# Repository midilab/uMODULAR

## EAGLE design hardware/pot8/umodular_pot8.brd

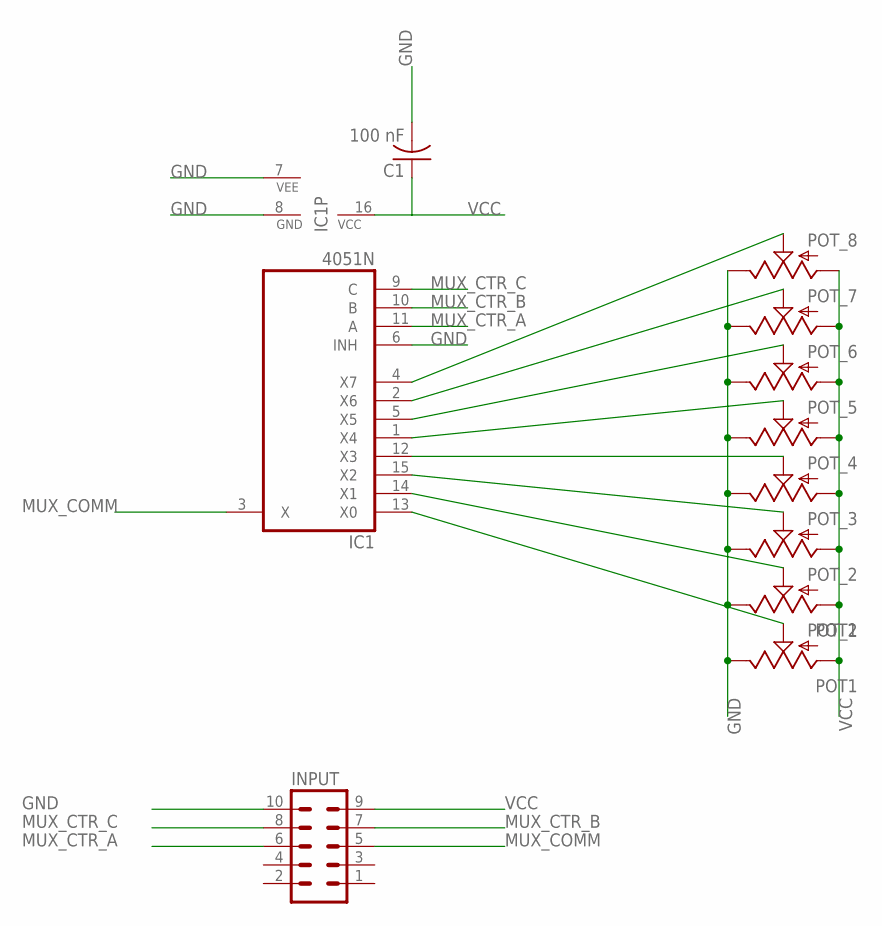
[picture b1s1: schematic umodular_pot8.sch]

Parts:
C1: 100 nF; C050-024X044
IC1: 4051N; DIL16
INPUT: MA05-2
POT_1: POT1; ALPS_POT
POT_2: POT2; ALPS_POT
POT_3, POT_4, POT_5, POT_6, POT_7, POT_8: POT; ALPS_POT

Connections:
GND: C1.2, IC1.6 (INH), IC1.7 (VEE), IC1.8 (GND), INPUT.10, POT_1.P$1 (E), POT_2.P$1 (E), POT_3.P$1 (E), POT_4.P$1 (E), POT_5.P$1 (E), POT_6.P$1 (E), POT_7.P$1 (E), POT_8.P$1 (E)
MUX_COMM: IC1.3 (X), INPUT.5
MUX_CTR_A: IC1.11 (A), INPUT.6
MUX_CTR_B: IC1.10 (B), INPUT.7
MUX_CTR_C: IC1.9 (C), INPUT.8
unnamed: IC1.5 (X5), POT_6.P$2 (S)
unnamed: IC1.2 (X6), POT_7.P$2 (S)
unnamed: IC1.13 (X0), POT_1.P$2 (S)
unnamed: IC1.14 (X1), POT_2.P$2 (S)
unnamed: IC1.15 (X2), POT_3.P$2 (S)
unnamed: IC1.12 (X3), POT_4.P$2 (S)
unnamed: IC1.1 (X4), POT_5.P$2 (S)
unnamed: IC1.4 (X7), POT_8.P$2 (S)
VCC: C1.1, IC1.16 (VCC), INPUT.9, POT_1.P$3 (A), POT_2.P$3 (A), POT_3.P$3 (A), POT_4.P$3 (A), POT_5.P$3 (A), POT_6.P$3 (A), POT_7.P$3 (A), POT_8.P$3 (A)

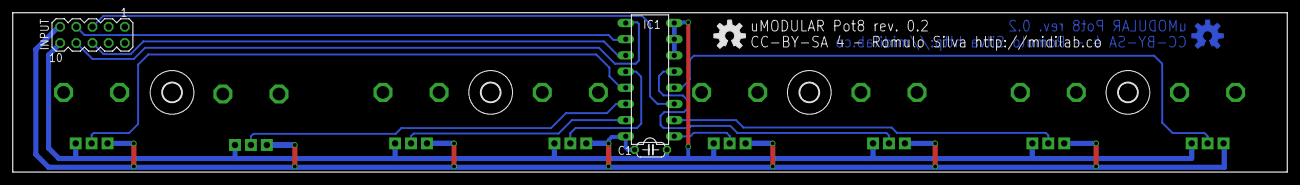
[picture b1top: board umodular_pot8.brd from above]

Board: 2 copper layers, 200.0 x 25.0 mm, 17 parts (0 on the bottom side), 14 nets.

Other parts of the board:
U$1, U$2, U$3, U$4: 3,0
U$5, U$6: OSHW-LOGO-M

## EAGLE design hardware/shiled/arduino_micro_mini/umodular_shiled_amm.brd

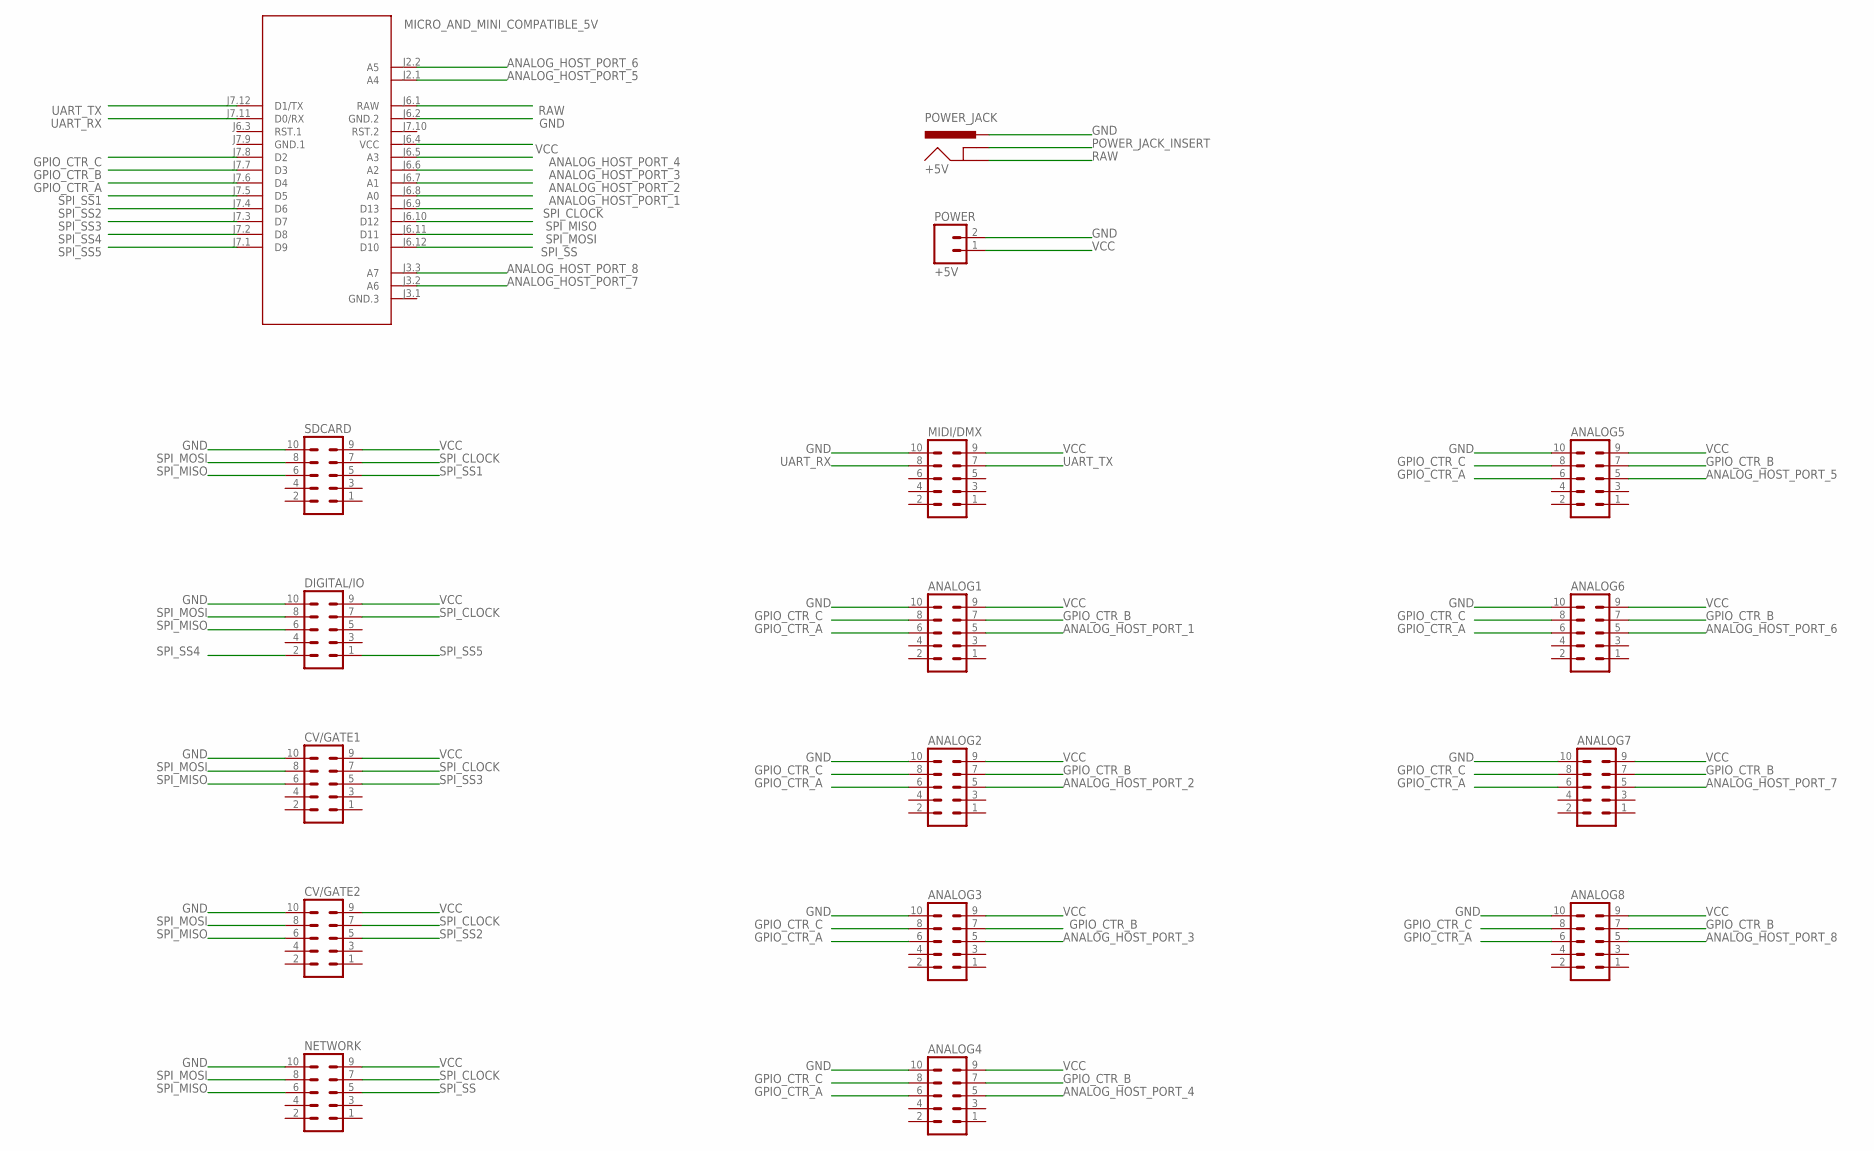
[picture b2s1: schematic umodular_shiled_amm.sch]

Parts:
+5V: POWER_JACK; POWER_JACK_PTH
ANALOG1, ANALOG2, ANALOG3, ANALOG4, ANALOG5, ANALOG6, ANALOG7, ANALOG8: MA05-2
CV/GATE1, CV/GATE2: MA05-2
DIGITAL/IO: MA05-2
MICRO_AND_MINI_COMPATIBLE_5V: ARDUINO-PRO-MINI-3.3V#NP; ARDUINO-PRO-MINI#NP
MIDI/DMX: MA05-2
NETWORK: MA05-2
POWER: +5V; 1X02_LOCK_LONGPADS
SDCARD: MA05-2

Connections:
ANALOG_HOST_PORT_1: ANALOG1.5, MICRO_AND_MINI_COMPATIBLE_5V.J6.8 (A0)
ANALOG_HOST_PORT_2: ANALOG2.5, MICRO_AND_MINI_COMPATIBLE_5V.J6.7 (A1)
ANALOG_HOST_PORT_3: ANALOG3.5, MICRO_AND_MINI_COMPATIBLE_5V.J6.6 (A2)
ANALOG_HOST_PORT_4: ANALOG4.5, MICRO_AND_MINI_COMPATIBLE_5V.J6.5 (A3)
ANALOG_HOST_PORT_5: ANALOG5.5, MICRO_AND_MINI_COMPATIBLE_5V.J2.1 (A4)
ANALOG_HOST_PORT_6: ANALOG6.5, MICRO_AND_MINI_COMPATIBLE_5V.J2.2 (A5)
ANALOG_HOST_PORT_7: ANALOG7.5, MICRO_AND_MINI_COMPATIBLE_5V.J3.2 (A6)
ANALOG_HOST_PORT_8: ANALOG8.5, MICRO_AND_MINI_COMPATIBLE_5V.J3.3 (A7)
GND: +5V.PWR, ANALOG1.10, ANALOG2.10, ANALOG3.10, ANALOG4.10, ANALOG5.10, ANALOG6.10, ANALOG7.10, ANALOG8.10, CV/GATE1.10, CV/GATE2.10, DIGITAL/IO.10, MICRO_AND_MINI_COMPATIBLE_5V.J6.2 (GND.2), MIDI/DMX.10, NETWORK.10, POWER.2, SDCARD.10
GND.1: MICRO_AND_MINI_COMPATIBLE_5V.J7.9 (GND.1)
GPIO_CTR_A: ANALOG1.6, ANALOG2.6, ANALOG3.6, ANALOG4.6, ANALOG5.6, ANALOG6.6, ANALOG7.6, ANALOG8.6, MICRO_AND_MINI_COMPATIBLE_5V.J7.6 (D4)
GPIO_CTR_B: ANALOG1.7, ANALOG2.7, ANALOG3.7, ANALOG4.7, ANALOG5.7, ANALOG6.7, ANALOG7.7, ANALOG8.7, MICRO_AND_MINI_COMPATIBLE_5V.J7.7 (D3)
GPIO_CTR_C: ANALOG1.8, ANALOG2.8, ANALOG3.8, ANALOG4.8, ANALOG5.8, ANALOG6.8, ANALOG7.8, ANALOG8.8, MICRO_AND_MINI_COMPATIBLE_5V.J7.8 (D2)
POWER_JACK_INSERT: +5V.GNDBREAK
RAW: +5V.GND, MICRO_AND_MINI_COMPATIBLE_5V.J6.1 (RAW)
SPI_CLOCK: CV/GATE1.7, CV/GATE2.7, DIGITAL/IO.7, MICRO_AND_MINI_COMPATIBLE_5V.J6.9 (D13), NETWORK.7, SDCARD.7
SPI_MISO: CV/GATE1.6, CV/GATE2.6, DIGITAL/IO.6, MICRO_AND_MINI_COMPATIBLE_5V.J6.10 (D12), NETWORK.6, SDCARD.6
SPI_MOSI: CV/GATE1.8, CV/GATE2.8, DIGITAL/IO.8, MICRO_AND_MINI_COMPATIBLE_5V.J6.11 (D11), NETWORK.8, SDCARD.8
SPI_SS: MICRO_AND_MINI_COMPATIBLE_5V.J6.12 (D10), NETWORK.5
SPI_SS1: MICRO_AND_MINI_COMPATIBLE_5V.J7.5 (D5), SDCARD.5
SPI_SS2: CV/GATE2.5, MICRO_AND_MINI_COMPATIBLE_5V.J7.4 (D6)
SPI_SS3: CV/GATE1.5, MICRO_AND_MINI_COMPATIBLE_5V.J7.3 (D7)
SPI_SS4: DIGITAL/IO.2, MICRO_AND_MINI_COMPATIBLE_5V.J7.2 (D8)
SPI_SS5: DIGITAL/IO.1, MICRO_AND_MINI_COMPATIBLE_5V.J7.1 (D9)
UART_RX: MICRO_AND_MINI_COMPATIBLE_5V.J7.11 (D0/RX), MIDI/DMX.8
UART_TX: MICRO_AND_MINI_COMPATIBLE_5V.J7.12 (D1/TX), MIDI/DMX.7
VCC: ANALOG1.9, ANALOG2.9, ANALOG3.9, ANALOG4.9, ANALOG5.9, ANALOG6.9, ANALOG7.9, ANALOG8.9, CV/GATE1.9, CV/GATE2.9, DIGITAL/IO.9, MICRO_AND_MINI_COMPATIBLE_5V.J6.4 (VCC), MIDI/DMX.9, NETWORK.9, POWER.1, SDCARD.9

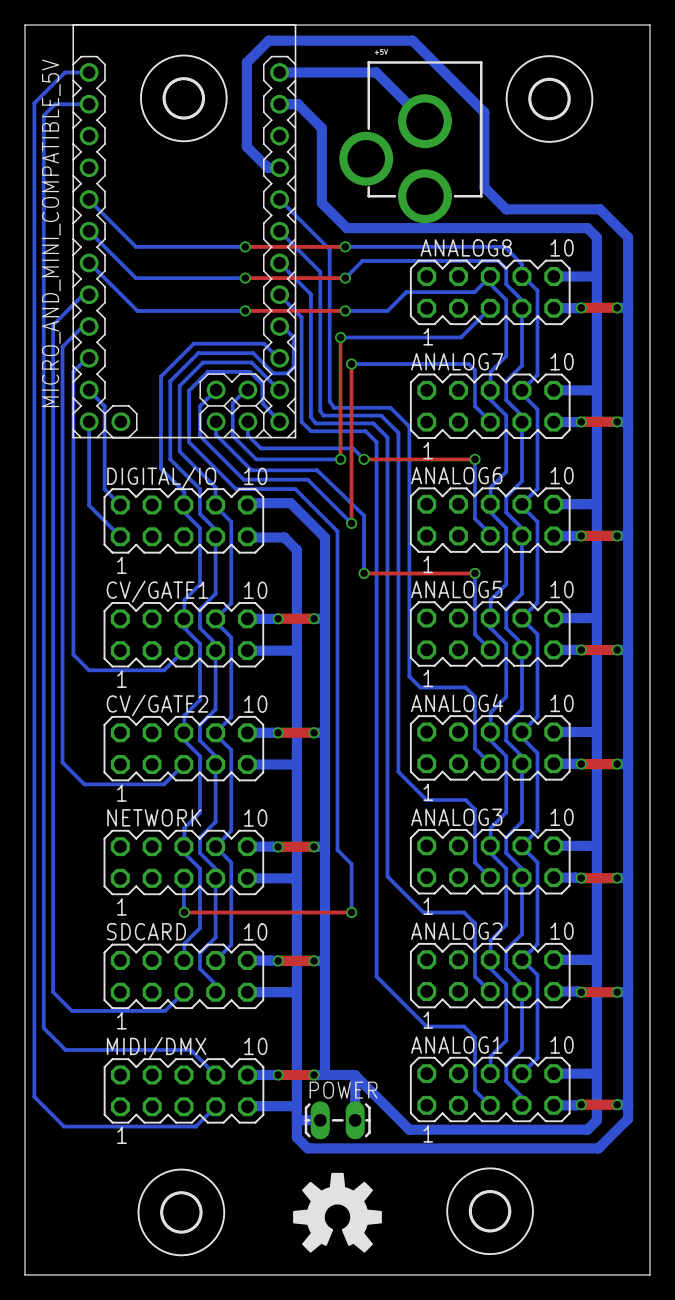
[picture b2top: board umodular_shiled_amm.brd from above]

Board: 2 copper layers, 50.0 x 100.0 mm, 22 parts (0 on the bottom side), 25 nets.

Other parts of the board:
U$1, U$2, U$3, U$4: 3,0
U$5: OSHW-LOGO-L

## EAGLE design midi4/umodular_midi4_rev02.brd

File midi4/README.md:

# midi4 module

midi4 is a 10cmx2.5cm PCB module for uMODULAR platform that supports 2 MIDI Ins and 2 MIDI Outs ports.

## BOM list

MIDI Connector
Circular DIN Connectors 5P R/A PCB SHIELDED 5mm CIRC DIN RECPT x4

IC
Optocoupler 6N138 x2
Socket 8P DUAL WIPE x2

Metal Film Resistors 1/4W Resistors
4.7k x2
220 x6
1k x2

Diode
1N4148TR x2

Headers & Wire Housings
05+05 DIL VERTICAL PIN HEADER x1

Cable connection with uMODULAR base
Ribbon Cable 10 Conductors 28 AWG .050
Female Ribbon Cable Header 10 Position, 2 rows, 2.54 mm pitch x2

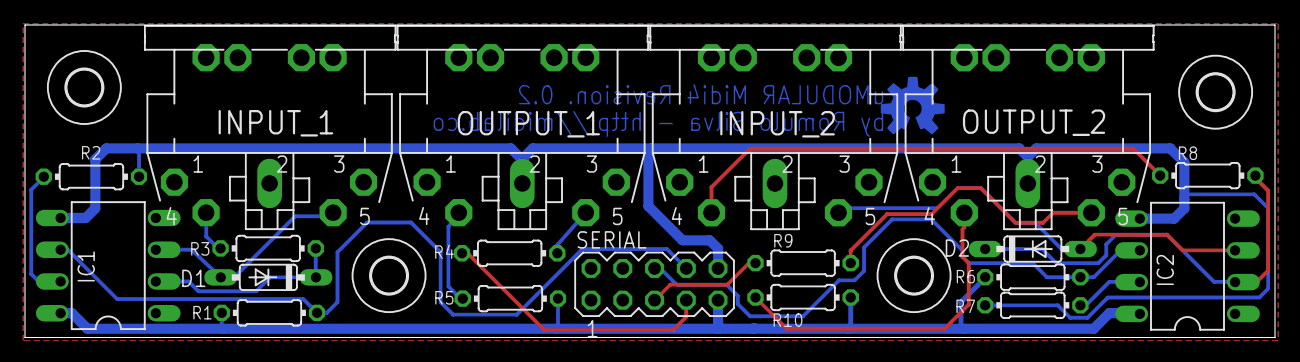
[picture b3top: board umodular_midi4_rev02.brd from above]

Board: 2 copper layers, 100.0 x 25.0 mm, 24 parts (0 on the bottom side), 18 nets.

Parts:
D1, D2: DO35-7
IC1, IC2: 6N138; DIL08
INPUT_1, INPUT_2: MIDI; CP-2350
OUTPUT_1, OUTPUT_2: MIDI; CP-2350
R1, R6: 1k; 0204/7@1
R2, R7: 4.7k; 0204/7@1
R3, R4, R5, R8, R9, R10: 220; 0204/7@1
SERIAL: MA05-2
U$1, U$2, U$3, U$4: 2,8
U$6: OSHW-LOGO-M_COPPER

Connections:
GND: IC1.5, IC2.5, OUTPUT_1.2, OUTPUT_2.2, R2.1, R7.1, SERIAL.10
MIDI_IN1: IC1.6, R1.2, SERIAL.8
MIDI_IN2: IC2.6, R6.2, SERIAL.6
MIDI_OUT1: R4.1, SERIAL.7
MIDI_OUT2: R9.1, SERIAL.5
unnamed: OUTPUT_2.4, R10.1
unnamed: OUTPUT_2.5, R9.2
unnamed: INPUT_2.4, R8.1
unnamed: D2.C, IC2.2, R8.2
unnamed: D2.A, IC2.3, INPUT_2.5
unnamed: IC2.7, R7.2
unnamed: INPUT_1.4, R3.1
unnamed: OUTPUT_1.4, R5.1
unnamed: OUTPUT_1.5, R4.2
unnamed: D1.C, IC1.2, R3.2
unnamed: D1.A, IC1.3, INPUT_1.5
unnamed: IC1.7, R2.2
VCC: IC1.8, IC2.8, R1.1, R5.2, R6.1, R10.2, SERIAL.9

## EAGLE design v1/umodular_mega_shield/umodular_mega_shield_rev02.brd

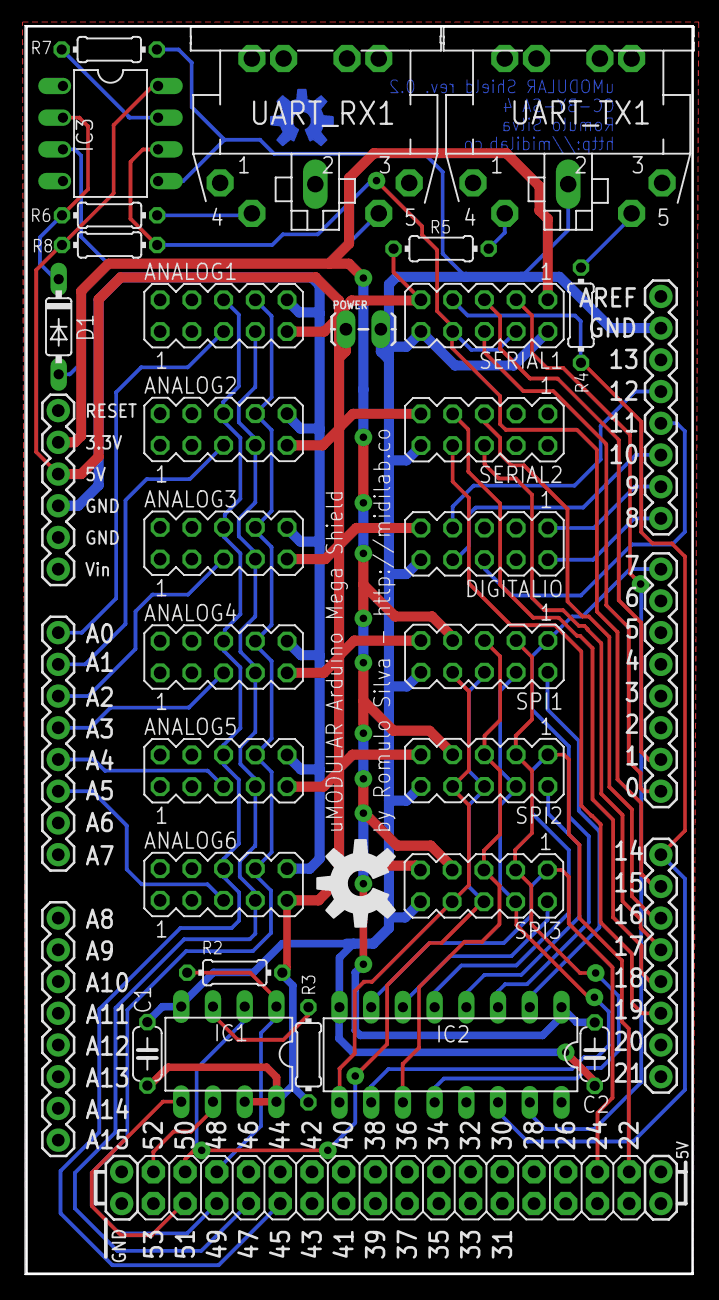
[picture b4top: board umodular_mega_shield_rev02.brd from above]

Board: 2 copper layers, 53.5 x 100.0 mm, 31 parts (0 on the bottom side), 49 nets.

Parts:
ANALOG1, ANALOG2, ANALOG3, ANALOG4, ANALOG5, ANALOG6: MA05-2
C1, C2: 100nf; C050-024X044
D1: DO35-7
DIGITALIO: MA05-2
IC1: 23LC1024; DIL08
IC2: 74HC4050/CD4050; DIL16
IC3: 6N138; DIL08
POWER: +5V; 1X02_LOCK_LONGPADS
R2, R3: 10k; 0204/7@1
R4, R5, R6: 220; 0204/7@1
R7: 4.7k; 0204/7@1
R8: 1k; 0204/7@1
SERIAL1, SERIAL2: MA05-2
SPI1, SPI2, SPI3: MA05-2
U1: ARDUINO-MEGA-SHIELD; ARDUINO_MEGA@1
U$1: OSHW-LOGO-M
U$5: OSHW-LOGO-L
UART_RX1: INPUT; CP-2350
UART_TX1: OUTPUT; CP-2350

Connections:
AGND: ANALOG1.10, ANALOG2.10, ANALOG3.10, ANALOG4.10, ANALOG5.10, ANALOG6.10, U1.GND@0
ANALOG_HOST_PORT_1: ANALOG1.5, U1.A0
ANALOG_HOST_PORT_2: ANALOG2.5, U1.A1
ANALOG_HOST_PORT_3: ANALOG3.5, U1.A2
ANALOG_HOST_PORT_4: ANALOG4.5, U1.A3
ANALOG_HOST_PORT_5: ANALOG5.5, U1.A4
ANALOG_HOST_PORT_6: ANALOG6.5, U1.A5
GND: C1.1, C2.1, DIGITALIO.10, IC1.4, IC2.8, IC3.5, POWER.2, R7.1, SERIAL1.2, SERIAL1.10, SERIAL2.10, SPI1.10, SPI2.10, SPI3.10, U1.GND@4, UART_TX1.2
GPIO_CTR_A: ANALOG1.6, ANALOG2.6, ANALOG3.6, ANALOG4.6, ANALOG5.6, ANALOG6.6, U1.45
GPIO_CTR_B: ANALOG1.7, ANALOG2.7, ANALOG3.7, ANALOG4.7, ANALOG5.7, ANALOG6.7, U1.47
GPIO_CTR_C: ANALOG1.8, ANALOG2.8, ANALOG3.8, ANALOG4.8, ANALOG5.8, ANALOG6.8, U1.49
LATCH_165: DIGITALIO.1, U1.9
LATCH_595: DIGITALIO.2, U1.8
unnamed: R5.1, UART_TX1.4
unnamed: R4.2, UART_TX1.5
unnamed: IC1.3, R3.2
unnamed: R6.1, UART_RX1.4
unnamed: D1.C, IC3.2, R6.2
unnamed: D1.A, IC3.3, UART_RX1.5
unnamed: IC3.7, R7.2
SDCARD_CLOCK: IC2.11, U1.39
SDCARD_MISO: SPI1.6, U1.40
SDCARD_MOSI: IC2.9, U1.38
SPI_CLOCK: IC1.6, SPI1.5, SPI2.5, SPI3.5, U1.52
SPI_CLOCK_3_3V: IC2.12, SPI1.3, SPI2.3, SPI3.3
SPI_MEM_SS: IC1.1, R2.2, U1.48
SPI_MISO: IC1.2, SPI2.6, SPI3.6, U1.50
SPI_MOSI: IC1.5, SPI1.8, SPI2.8, SPI3.8, U1.51
SPI_MOSI_3_3V: IC2.10, SPI1.4, SPI2.4, SPI3.4
SPI_SS1: IC2.3, SPI1.1, U1.7
SPI_SS1_3_3V: IC2.2, SPI1.2
SPI_SS2: IC2.5, SPI2.1, U1.22
SPI_SS2_3_3V: IC2.4, SPI2.2
SPI_SS3: IC2.7, SPI3.1, U1.24
SPI_SS3_3_3V: IC2.6, SPI3.2
SR_CLOCK: DIGITALIO.7, U1.12
SR_DATA_165: DIGITALIO.6, U1.11
SR_DATA_595: DIGITALIO.8, U1.10
UART_RX0: SERIAL1.6, U1.0
UART_RX1: SERIAL2.8, U1.19
UART_RX2: SERIAL2.6, U1.17
UART_RX3: IC3.6, R8.2, SERIAL1.4, SERIAL1.8, U1.15
UART_TX0: SERIAL1.5, U1.1
UART_TX1: SERIAL2.7, U1.18
UART_TX2: SERIAL2.5, U1.16
UART_TX3: IC2.14, R4.1, SERIAL1.7, U1.14
UART_TX3_3_3V: IC2.15, SERIAL1.3
VCC: ANALOG1.9, ANALOG2.9, ANALOG3.9, ANALOG4.9, ANALOG5.9, ANALOG6.9, C1.2, DIGITALIO.9, IC1.7, IC1.8, IC3.8, POWER.1, R2.1, R3.1, R5.2, R8.1, SERIAL1.9, SERIAL2.9, SPI1.9, SPI2.9, SPI3.9, U1.5V@0
VCC_3_3V: C2.2, IC2.1, SERIAL1.1, SPI1.7, SPI2.7, SPI3.7, U1.3.3V

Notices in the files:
hardware/pot8/umodular_pot8.brd:
CC-BY-SA 4 - Romulo Silva http://midilab.co
hardware/shiled/arduino_micro_mini/umodular_shiled_amm.brd:
CC-BY-SA 4
parts and their libraries:
SparkFun-Electromechanical_mod: Licensing: CC v3.0 Share-Alike You are welcome to use this library for commercial purposes.
diy-modules: Released under the Creative Commons Attribution 4.0 International License: http://creativecommons.org/licenses/by/4.0
